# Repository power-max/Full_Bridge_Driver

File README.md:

# Full_Bridge_Driver
This project is intended as the high voltage H-bridge of a 300KHz tesla coil, although it could be used for other things.

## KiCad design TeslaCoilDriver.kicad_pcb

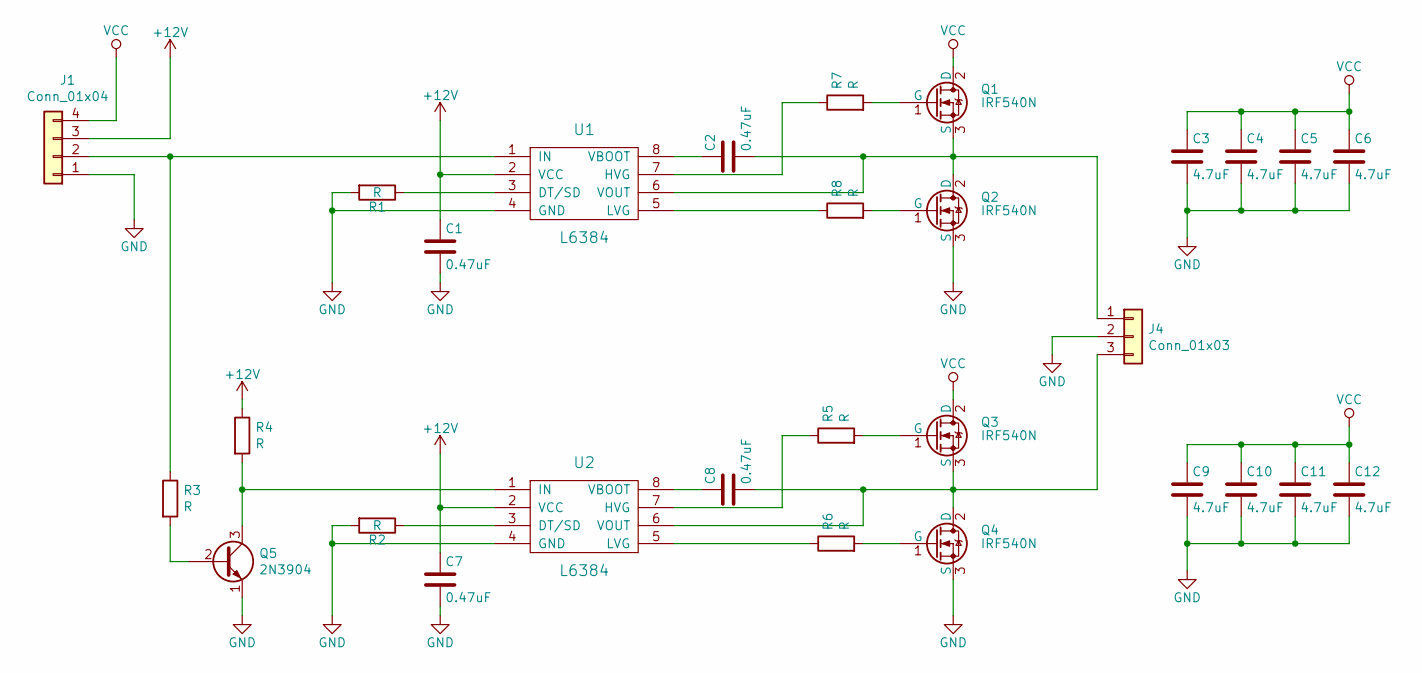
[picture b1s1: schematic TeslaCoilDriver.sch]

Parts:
C1, C2, C7, C8: 0.47uF; C_1206
C3, C4, C5, C6, C9, C10, C11, C12: 4.7uF; C_1206
J1: Conn_01x04; JST_NV_B04P-NV_4x5.00mm_Vertical
J4: Conn_01x03; JST_NV_B03P-NV_3x5.00mm_Vertical
Q1, Q2, Q3, Q4: IRF540N; TO-220-3_Vertical
Q5: 2N3904; SOT-23
R1, R2, R3, R4, R5, R6, R7, R8: R; R_1206
U1, U2: L6384; SO-8_5.3x6.2mm_Pitch1.27mm

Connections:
+12V: C1.1, C7.1, J1.3, R4.1, U1.2 (VCC), U2.2 (VCC)
GND: C1.2, C3.2, C4.2, C5.2, C6.2, C7.2, C9.2, C10.2, C11.2, C12.2, J1.1, J4.2, Q2.3 (S), Q4.3 (S), Q5.1 (E), R1.2, R2.2, U1.4 (GND), U2.4 (GND)
unnamed: C2.1, U1.8 (VBOOT)
unnamed: C2.2, J4.1, Q1.3 (S), Q2.2 (D), U1.6 (VOUT)
unnamed: C8.1, U2.8 (VBOOT)
unnamed: C8.2, J4.3, Q3.3 (S), Q4.2 (D), U2.6 (VOUT)
unnamed: J1.2, R3.1, U1.1 (IN)
unnamed: Q1.1 (G), R7.2
unnamed: Q2.1 (G), R8.2
unnamed: Q3.1 (G), R5.2
unnamed: Q4.1 (G), R6.2
unnamed: Q5.2 (B), R3.2
unnamed: Q5.3 (C), R4.2, U2.1 (IN)
unnamed: R1.1, U1.3 (DT/SD)
unnamed: R2.1, U2.3 (DT/SD)
unnamed: R5.1, U2.7 (HVG)
unnamed: R6.1, U2.5 (LVG)
unnamed: R7.1, U1.7 (HVG)
unnamed: R8.1, U1.5 (LVG)
VCC: C3.1, C4.1, C5.1, C6.1, C9.1, C10.1, C11.1, C12.1, J1.4, Q1.2 (D), Q3.2 (D)

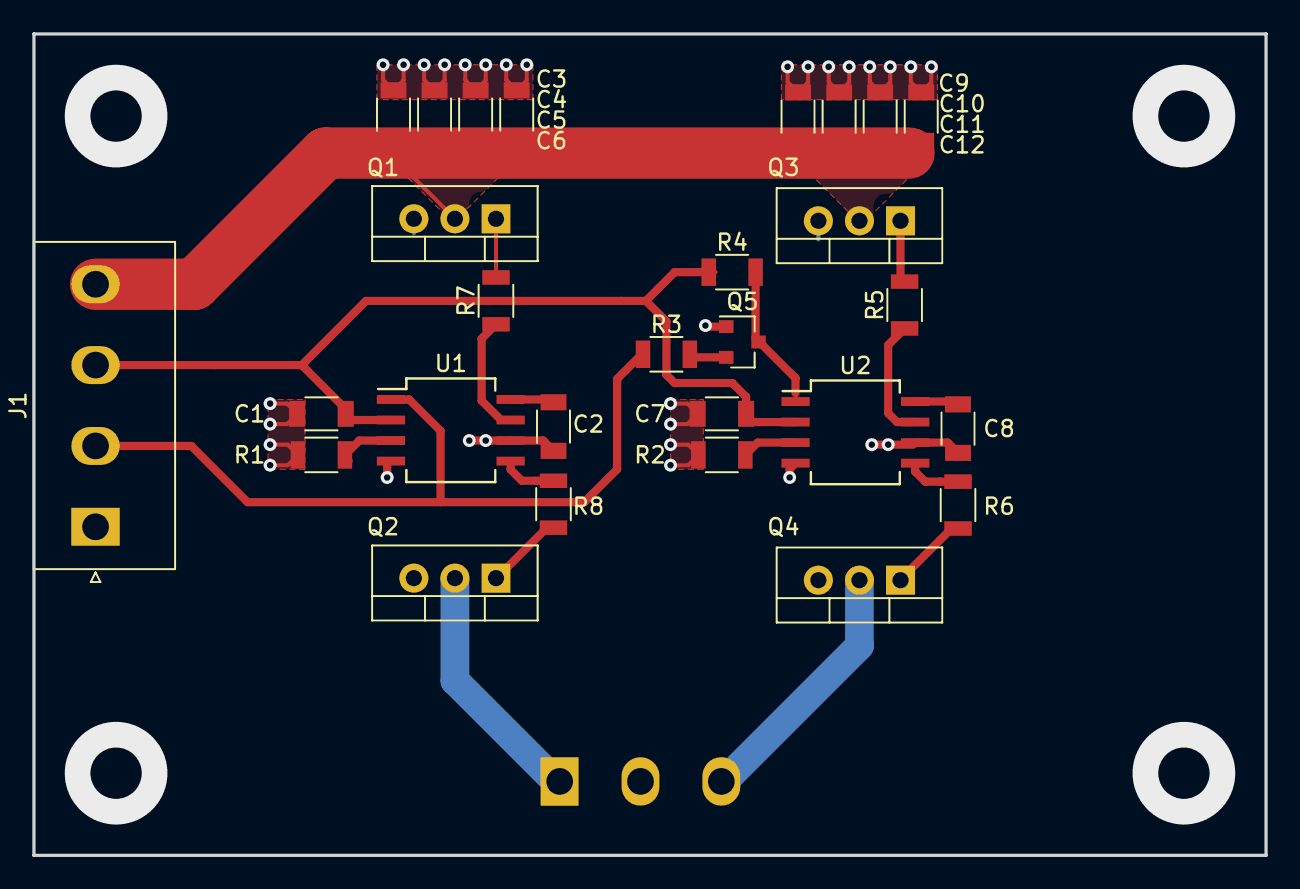
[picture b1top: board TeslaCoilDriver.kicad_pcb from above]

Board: 2 copper layers, 76.2 x 50.8 mm, 29 parts (1 on the bottom side), 20 nets.

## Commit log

2018-12-21 initial design
